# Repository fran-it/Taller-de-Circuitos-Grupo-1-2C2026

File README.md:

# Taller-de-Circuitos-Grupo-1-2C2026

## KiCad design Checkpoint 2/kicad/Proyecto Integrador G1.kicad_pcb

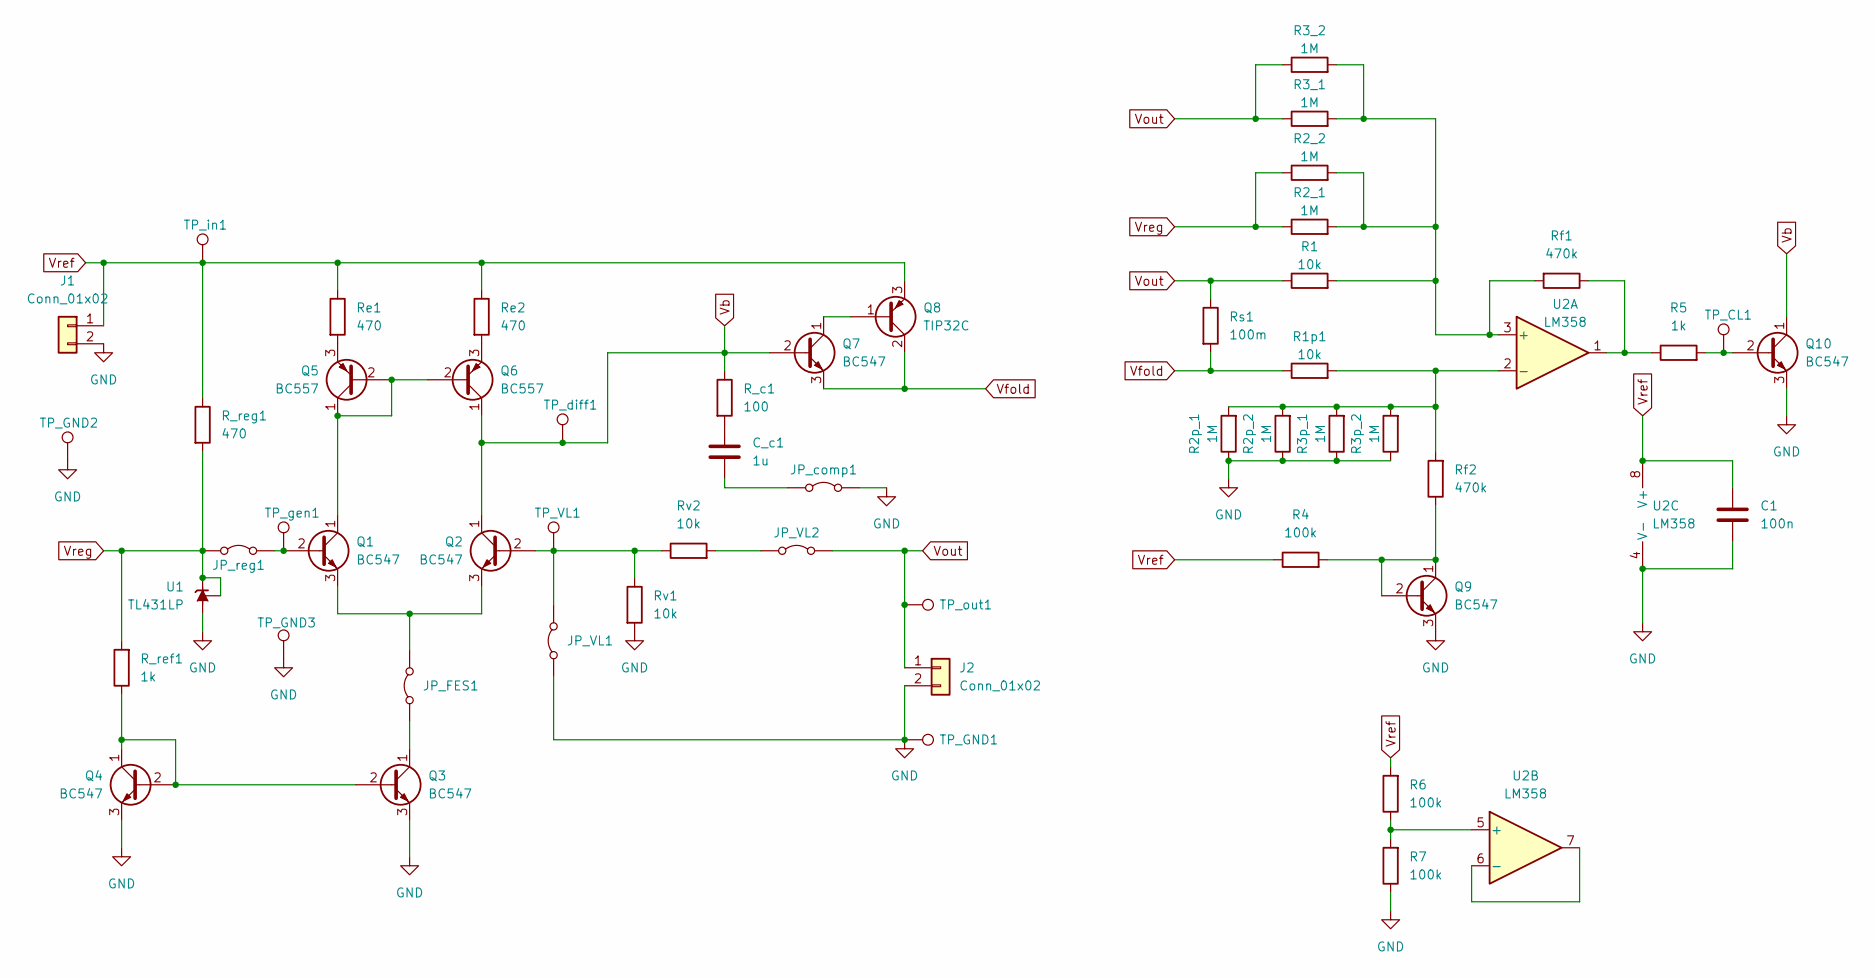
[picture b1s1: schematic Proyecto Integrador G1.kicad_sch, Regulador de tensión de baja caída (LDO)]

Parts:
C1: 100n; C_Disc_D5.0mm_W2.5mm_P2.50mm
C_c1: 1u; C_Disc_D5.0mm_W2.5mm_P2.50mm
J1, J2: Conn_01x02; Samtec_HPM-02-01-x-S_Straight_1x02_Pitch5.08mm
JP_FES1: Jumper_2_Bridged; TestPoint_2Pads_Pitch2.54mm_Drill0.8mm
JP_VL1, JP_VL2: Jumper_2_Bridged; TestPoint_2Pads_Pitch2.54mm_Drill0.8mm
JP_comp1: Jumper_2_Bridged; TestPoint_2Pads_Pitch2.54mm_Drill0.8mm
JP_reg1: Jumper_2_Bridged; TestPoint_2Pads_Pitch2.54mm_Drill0.8mm
Q1, Q2, Q3, Q4, Q7, Q9, Q10: BC547; TO-92_Inline_Wide
Q5, Q6: BC557; TO-92_Inline_Wide
Q8: TIP32C; TO-220-3_Vertical
R1, R1p1: 10k; R_Axial_DIN0207_L6.3mm_D2.5mm_P7.62mm_Horizontal
R2_1, R2_2, R2p_1, R2p_2, R3_1, R3_2, R3p_1, R3p_2: 1M; R_Axial_DIN0207_L6.3mm_D2.5mm_P7.62mm_Horizontal
R4, R6, R7: 100k; R_Axial_DIN0207_L6.3mm_D2.5mm_P7.62mm_Horizontal
R5: 1k; R_Axial_DIN0207_L6.3mm_D2.5mm_P7.62mm_Horizontal
R_c1: 100; R_Axial_DIN0207_L6.3mm_D2.5mm_P7.62mm_Horizontal
R_ref1: 1k; R_Axial_DIN0207_L6.3mm_D2.5mm_P7.62mm_Horizontal
R_reg1: 470; R_Axial_DIN0207_L6.3mm_D2.5mm_P7.62mm_Horizontal
Re1, Re2: 470; R_Axial_DIN0207_L6.3mm_D2.5mm_P7.62mm_Horizontal
Rf1, Rf2: 470k; R_Axial_DIN0207_L6.3mm_D2.5mm_P7.62mm_Horizontal
Rs1: 100m; R_Axial_Power_L20.0mm_W6.4mm_P22.40mm
Rv1, Rv2: 10k; R_Axial_DIN0207_L6.3mm_D2.5mm_P7.62mm_Horizontal
TP_CL1: TestPoint; PinHeader_1x01_P2.54mm_Vertical
TP_GND1, TP_GND2, TP_GND3: TestPoint; PinHeader_1x01_P2.54mm_Vertical
TP_VL1: TestPoint; PinHeader_1x01_P2.54mm_Vertical
TP_diff1: TestPoint; PinHeader_1x01_P2.54mm_Vertical
TP_gen1: TestPoint; PinHeader_1x01_P2.54mm_Vertical
TP_in1: TestPoint; PinHeader_1x01_P2.54mm_Vertical
TP_out1: TestPoint; PinHeader_1x01_P2.54mm_Vertical
U1: TL431LP; TO-92_Inline_Wide
U2: LM358

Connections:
GND: C1.2, J1.2, J2.2, JP_VL1.1 (A), JP_comp1.2 (B), Q3.3 (E), Q4.3 (E), Q9.3 (E), Q10.3 (E), R2p_1.1, R2p_2.1, R3p_1.1, R3p_2.1, R7.1, Rv1.2, TP_GND1.1 (1_1), TP_GND2.1 (1_1), TP_GND3.1 (1_1), U1.2 (A), U2.4 (V-)
unnamed: C_c1.1, R_c1.2
unnamed: JP_FES1.1 (A), Q3.1 (C)
unnamed: JP_FES1.2 (B), Q1.3 (E), Q2.3 (E)
unnamed: JP_VL1.2 (B), Q2.2 (B), Rv1.1, Rv2.1, TP_VL1.1 (1_1)
unnamed: JP_VL2.1 (A), Rv2.2
unnamed: C_c1.2, JP_comp1.1 (A)
unnamed: JP_reg1.2 (B), Q1.2 (B), TP_gen1.1 (1_1)
unnamed: Q1.1 (C), Q5.1 (C), Q5.2 (B), Q6.2 (B)
unnamed: Q3.2 (B), Q4.1 (C), Q4.2 (B), R_ref1.1
unnamed: Q5.3 (E), Re1.2
unnamed: Q6.3 (E), Re2.2
unnamed: Q7.1 (C), Q8.1 (B)
unnamed: Q9.1 (C), Q9.2 (B), R4.2, Rf2.1
unnamed: Q10.2 (B), R5.2, TP_CL1.1 (1_1)
unnamed: R5.1, Rf1.1, U2.1
unnamed: R1.2, R2_1.2, R2_2.2, R3_1.2, R3_2.2, Rf1.2, U2.3 (+)
unnamed: R1p1.2, R2p_1.2, R2p_2.2, R3p_1.2, R3p_2.2, Rf2.2, U2.2 (-)
unnamed: R6.1, R7.2, U2.5 (+)
unnamed: U2.6 (-), U2.7
Vb: Q2.1 (C), Q6.1 (C), Q7.2 (B), Q10.1 (C), R_c1.1, TP_diff1.1 (1_1)
Vfold: Q7.3 (E), Q8.2 (C), R1p1.1, Rs1.2
Vout: J2.1, JP_VL2.2 (B), R1.1, R3_1.1, R3_2.1, Rs1.1, TP_out1.1 (1_1)
Vref: C1.1, J1.1, Q8.3 (E), R4.1, R6.2, R_reg1.1, Re1.1, Re2.1, TP_in1.1 (1_1), U2.8 (V+)
Vreg: JP_reg1.1 (A), R2_1.1, R2_2.1, R_ref1.2, R_reg1.2, U1.1 (REF), U1.3 (K)

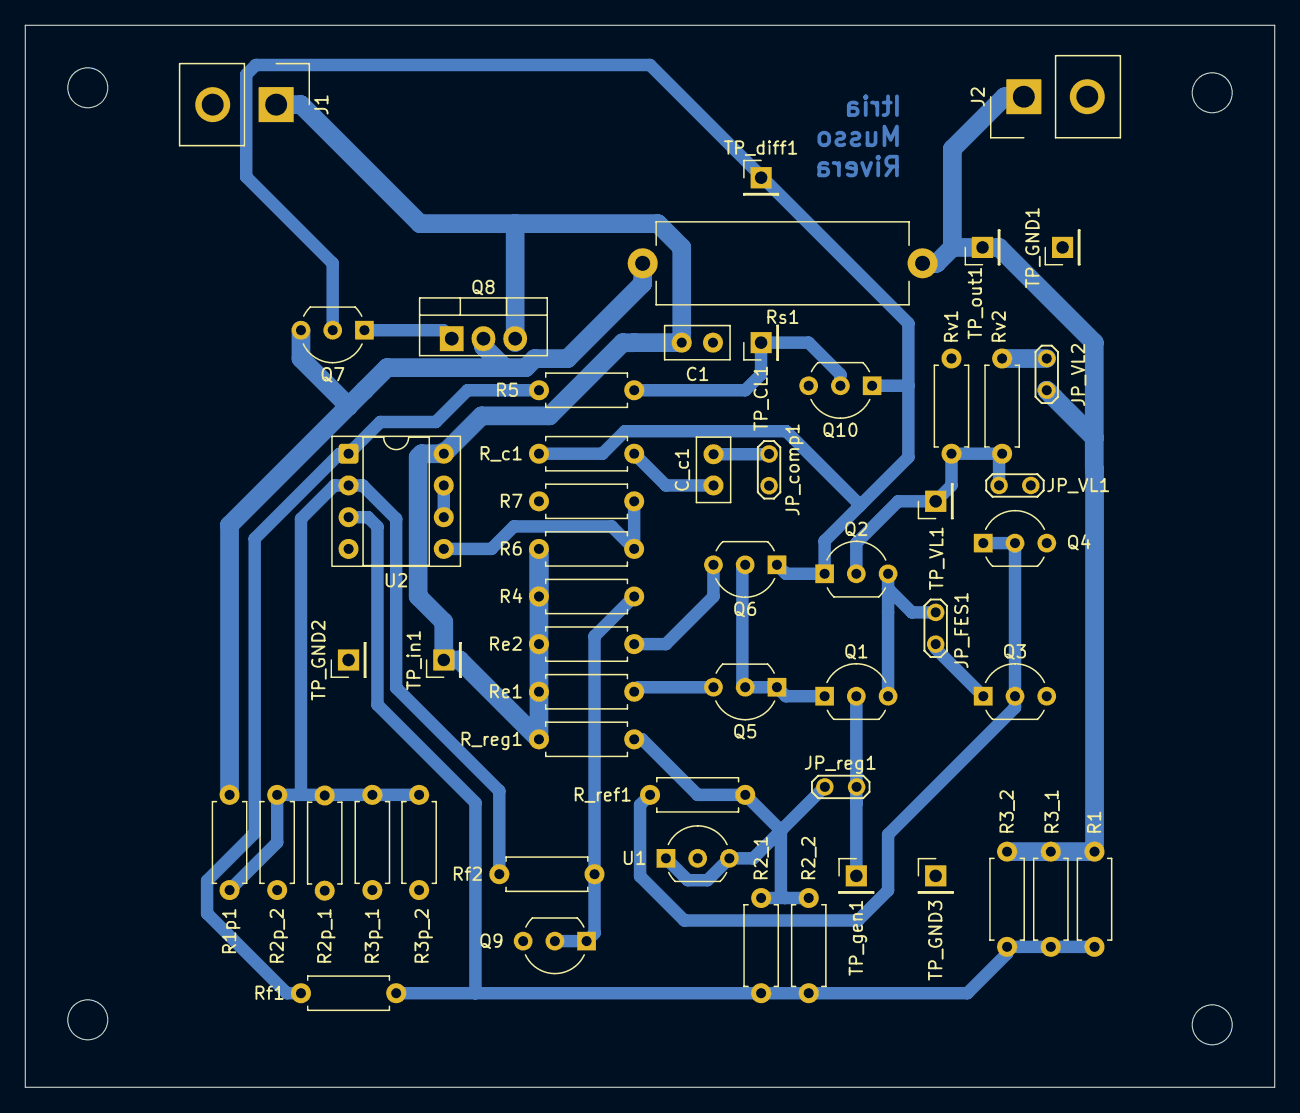
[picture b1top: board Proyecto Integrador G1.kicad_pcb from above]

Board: 2 copper layers, 100.0 x 85.0 mm, 54 parts (0 on the bottom side), 25 nets.
